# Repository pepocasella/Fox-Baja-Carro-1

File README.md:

# Fox-Baja-Carro-1
Projeto Elétrica: primeiro projeto da elétrica do fox baja IHM com raspberry pi 3 e tela Lcd 7 Oficial Raspberry Pi 800x480 Touch Screen

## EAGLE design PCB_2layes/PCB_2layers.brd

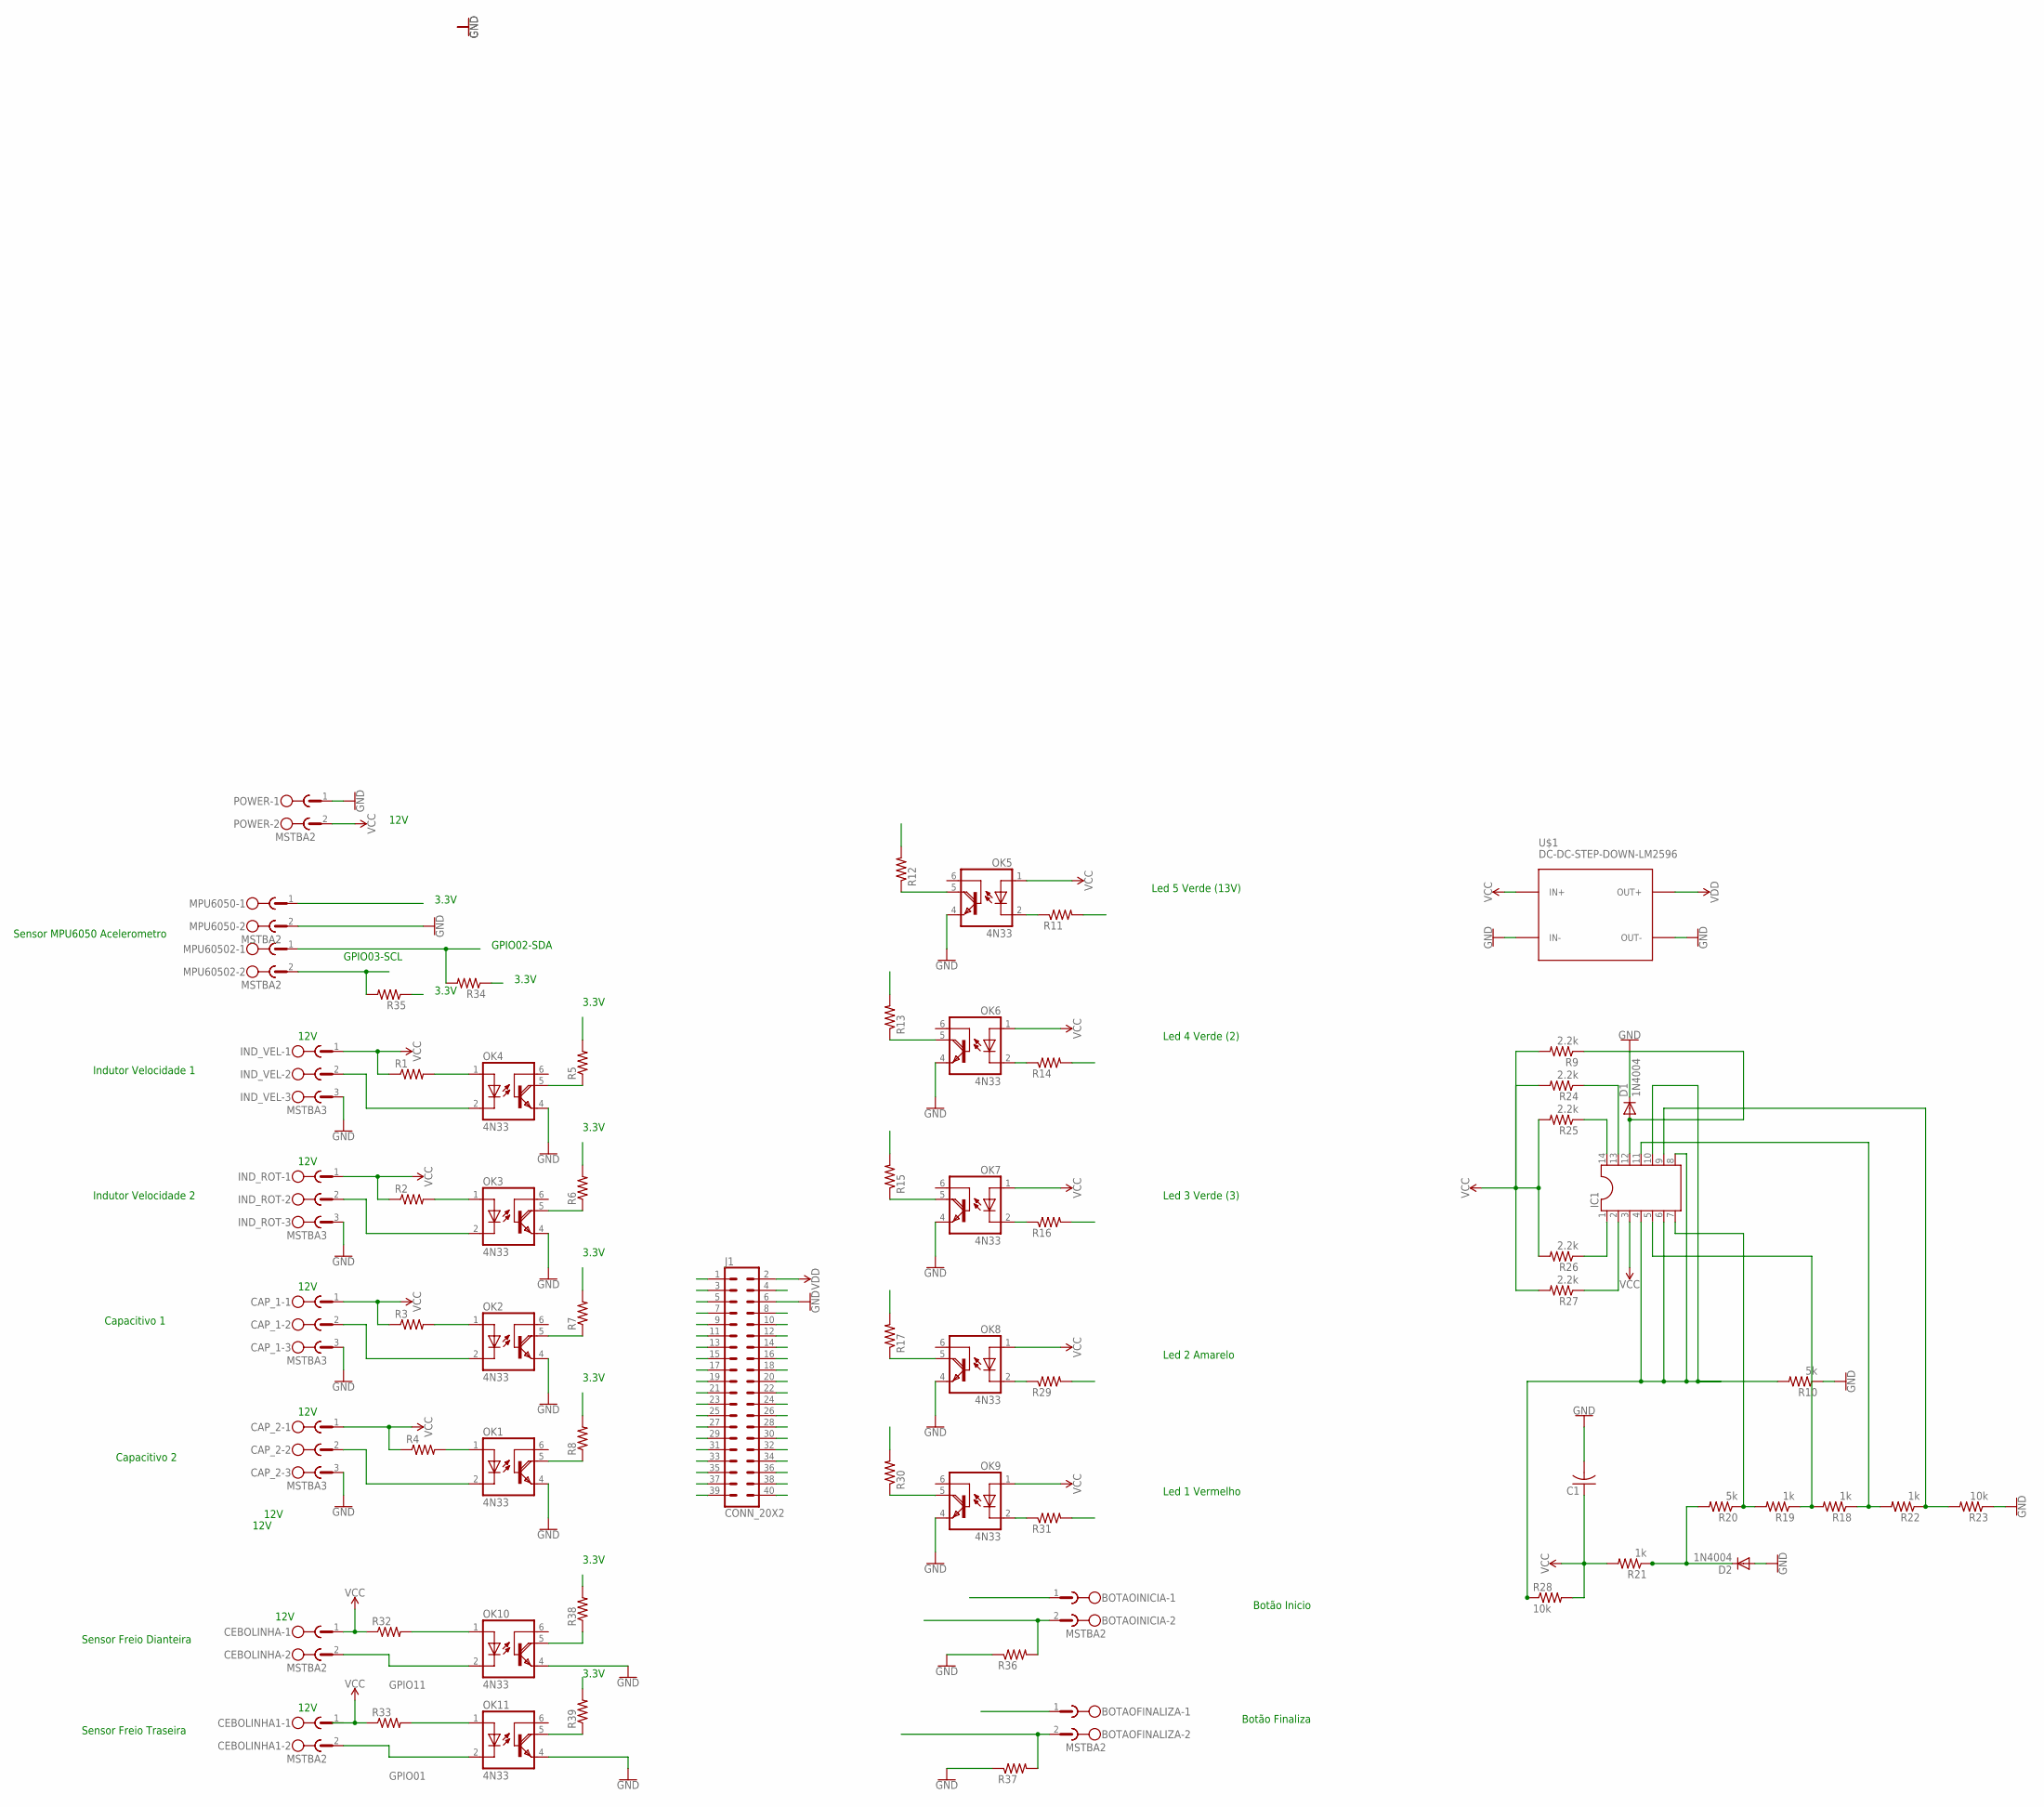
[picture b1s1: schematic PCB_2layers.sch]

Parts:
BOTAOFINALIZA: MSTBA2
BOTAOINICIA: MSTBA2
C1: C-US025-050X050; C025-050X050
CAP_1, CAP_2: MSTBA3
CEBOLINHA, CEBOLINHA1: MSTBA2
D1, D2: 1N4004; DO41-10
IC1: DIL14
IND_ROT: MSTBA3
IND_VEL: MSTBA3
J1: CONN_20X2; 2X20
MPU6050, MPU60502: MSTBA2
OK1, OK2, OK3, OK4, OK5, OK6, OK7, OK8, OK9, OK10, OK11: 4N33; DIL06
POWER: MSTBA2
R1, R2, R3, R4, R5, R6, R7, R8, R11, R12, R13, R14, R15, R16, R17, R29, R30, R31, R32, R33, R34, R35, R36, R37, R38, R39: R-US_0204/7; 0204/7
R9, R24, R25, R26, R27: 2.2k; 0207/10
R10, R20: 5k; 0207/10
R18, R19, R21, R22: 1k; 0207/10
R23, R28: 10k; 0207/10
U$1: DC-DC-STEP-DOWN-LM2596

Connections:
DC3.3V: BOTAOFINALIZA.1, BOTAOINICIA.1, J1.1, J1.17, MPU6050.1, R5.2, R6.2, R7.2, R8.2, R12.2, R13.2, R15.2, R17.2, R30.2, R34.1, R35.1, R38.2, R39.2
GND: C1.2, CAP_1.3, CAP_2.3, D1.C, D2.A, IND_ROT.3, IND_VEL.3, J1.6, J1.9, J1.14, J1.20, J1.25, J1.30, J1.34, OK1.4 (E), OK2.4 (E), OK3.4 (E), OK4.4 (E), OK5.4 (E), OK6.4 (E), OK7.4 (E), OK8.4 (E), OK9.4 (E), OK10.4 (E), OK11.4 (E), POWER.1, R10.1, R23.1, R36.1, R37.1, U$1.IN-, U$1.OUT-
GPIO01: CEBOLINHA1.2, OK11.2 (C)
GPIO02: J1.3
GPIO2: MPU60502.2, R35.2
GPIO03: J1.5, MPU60502.1, R34.2
GPIO04: J1.7, OK4.5 (COL), R5.1
GPIO05: J1.29
GPIO06: J1.31
GPIO07: J1.26
GPIO08: J1.24
GPIO09: J1.21
GPIO10: J1.19, OK1.5 (COL), R8.1
GPIO11: CEBOLINHA.2, J1.23, OK10.2 (C)
GPIO12: J1.32
GPIO13: J1.33
GPIO14: J1.8, OK5.5 (COL), R12.1
GPIO15: J1.10, OK6.5 (COL), R13.1
GPIO16: BOTAOINICIA.2, J1.36, R36.2
GPIO17: J1.11, OK3.5 (COL), R6.1
GPIO18: J1.12, OK7.5 (COL), R15.1
GPIO19: J1.35, OK10.5 (COL), R38.1
GPIO20: BOTAOFINALIZA.2, J1.38, R37.2
GPIO21: J1.40
GPIO22: J1.15, OK2.5 (COL), R7.1
GPIO23: J1.16, OK8.5 (COL), R17.1
GPIO24: J1.18, OK9.5 (COL), R30.1
GPIO25: J1.22
GPIO26: J1.37, OK11.5 (COL), R39.1
GPIO27: J1.13
ID_SC: J1.28
ID_SD: J1.27
LM339P1: IC1.1, R11.2, R26.1
LM339P2: IC1.2, R14.2, R27.1
LM339P12: R31.2
LM339P13: IC1.13, R16.2, R24.1
LM339P14: IC1.14, R25.1, R29.2
LM33912: D1.A, IC1.12, R9.1
unnamed: IND_ROT.2, OK3.2 (C)
unnamed: CAP_2.2, OK1.2 (C)
unnamed: CAP_1.2, OK2.2 (C)
unnamed: OK3.1 (A), R2.2
unnamed: OK2.1 (A), R3.2
unnamed: OK1.1 (A), R4.2
unnamed: OK4.1 (A), R1.2
unnamed: IND_VEL.2, OK4.2 (C)
unnamed: D2.C, R20.2, R21.1
unnamed: IC1.9, R22.1, R23.2
unnamed: IC1.4, IC1.6, IC1.8, IC1.10, R10.2, R28.1
unnamed: IC1.5, R18.2, R19.1
unnamed: IC1.11, R18.1, R22.2
unnamed: IC1.7, R19.2, R20.1
unnamed: OK5.2 (C), R11.1
unnamed: OK6.2 (C), R14.1
unnamed: OK10.1 (A), R32.2
unnamed: OK7.2 (C), R16.1
unnamed: OK8.2 (C), R29.1
unnamed: OK9.2 (C), R31.1
unnamed: OK11.1 (A), R33.2
VCC: C1.1, CAP_1.1, CAP_2.1, CEBOLINHA.1, CEBOLINHA1.1, IC1.3, IND_ROT.1, IND_VEL.1, OK5.1 (A), OK6.1 (A), OK7.1 (A), OK8.1 (A), OK9.1 (A), POWER.2, R1.1, R2.1, R3.1, R4.1, R9.2, R21.2, R24.2, R25.2, R26.2, R27.2, R28.2, R32.1, R33.1, U$1.IN+
VDD: J1.2, J1.4, U$1.OUT+

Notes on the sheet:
Indutor Velocidade 1
Indutor Velocidade 2
Capacitivo 1
Capacitivo 2
Led 5 Verde (13V)
Sensor Freio Dianteira
Sensor MPU6050 Acelerometro
Sensor Freio Traseira
Led 4 Verde (2)
Botão Inicio
Botão Finaliza
Led 3 Verde (3)
Led 2 Amarelo
Led 1 Vermelho
3.3V
12V
GPIO03-SCL
GPIO02-SDA

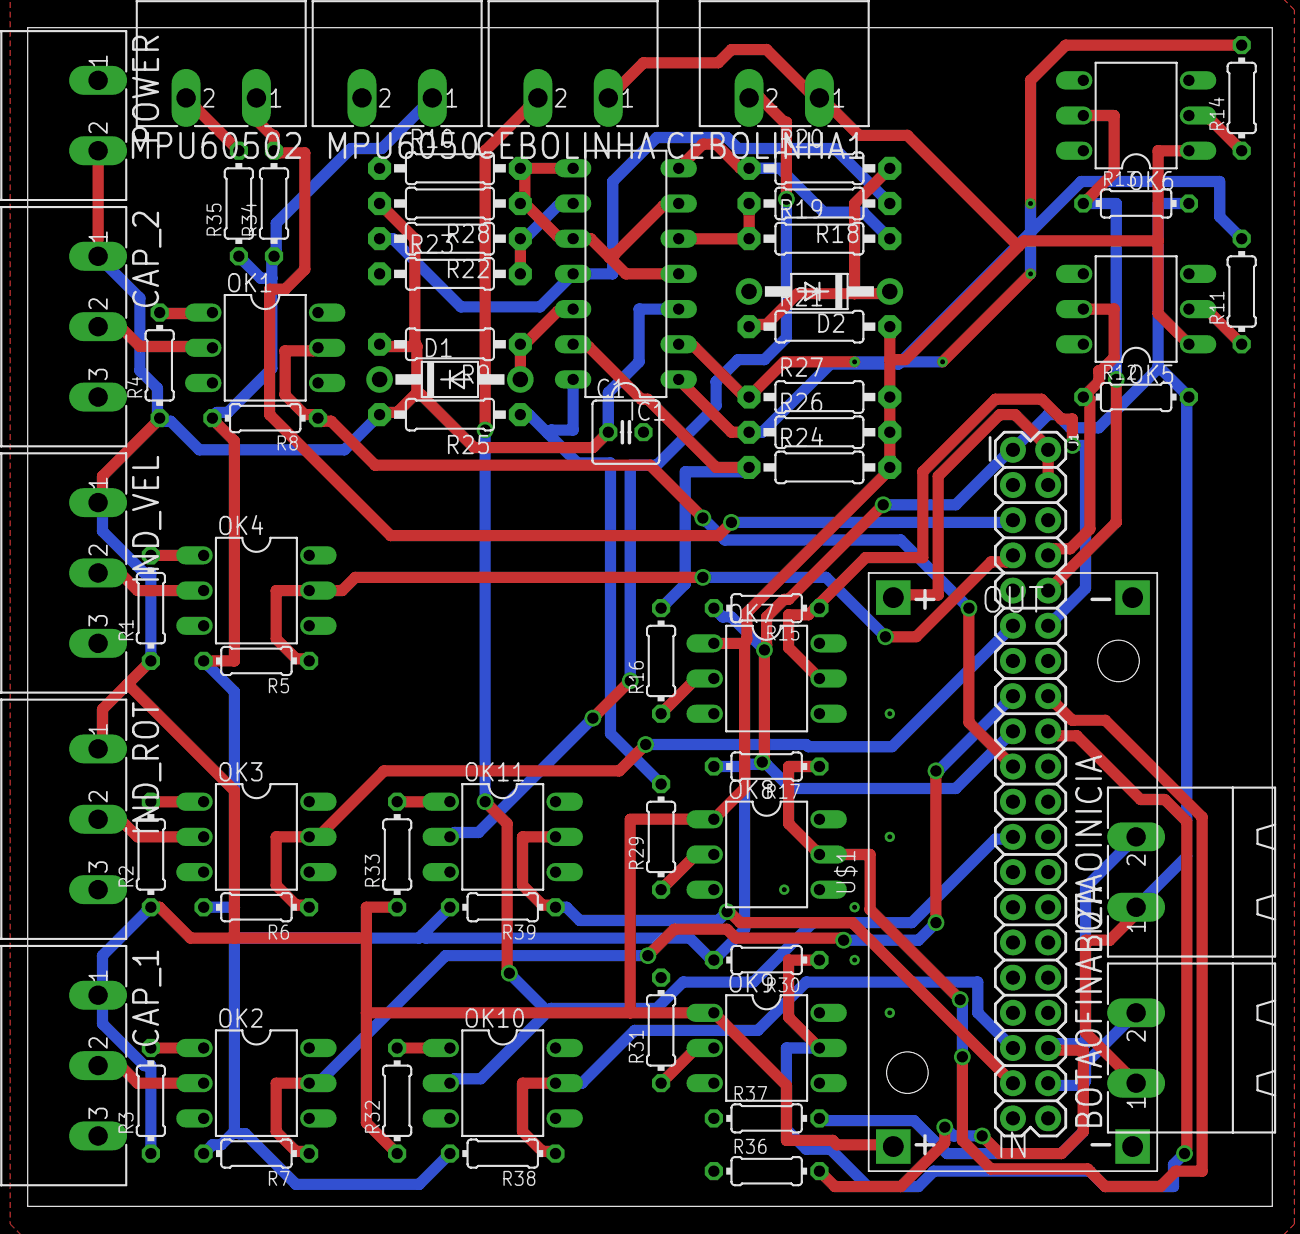
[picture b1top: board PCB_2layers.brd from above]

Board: 2 copper layers, 89.8 x 85.1 mm, 67 parts (0 on the bottom side), 47 nets.

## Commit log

2019-07-07 upload do primeiro projeto do carro baja do Insper. Cógigo em pyhton para raspberry com IHM idealizada. Circuito para aquisição de sinais de nivel do tanque da gasolina, giroscópio e velocidade do mo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
2019-07-07 upload de fotos

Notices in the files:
parts and their libraries:
SparkFun-Connectors: Licensing: Creative Commons ShareAlike 4.0 International - https://creativecommons.org/licenses/by-sa/4.0
diy-modules: Released under the Creative Commons Attribution 4.0 International License: http://creativecommons.org/licenses/by/4.0
